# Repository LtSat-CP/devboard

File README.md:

# devboard
DevBoard releases from LtSat

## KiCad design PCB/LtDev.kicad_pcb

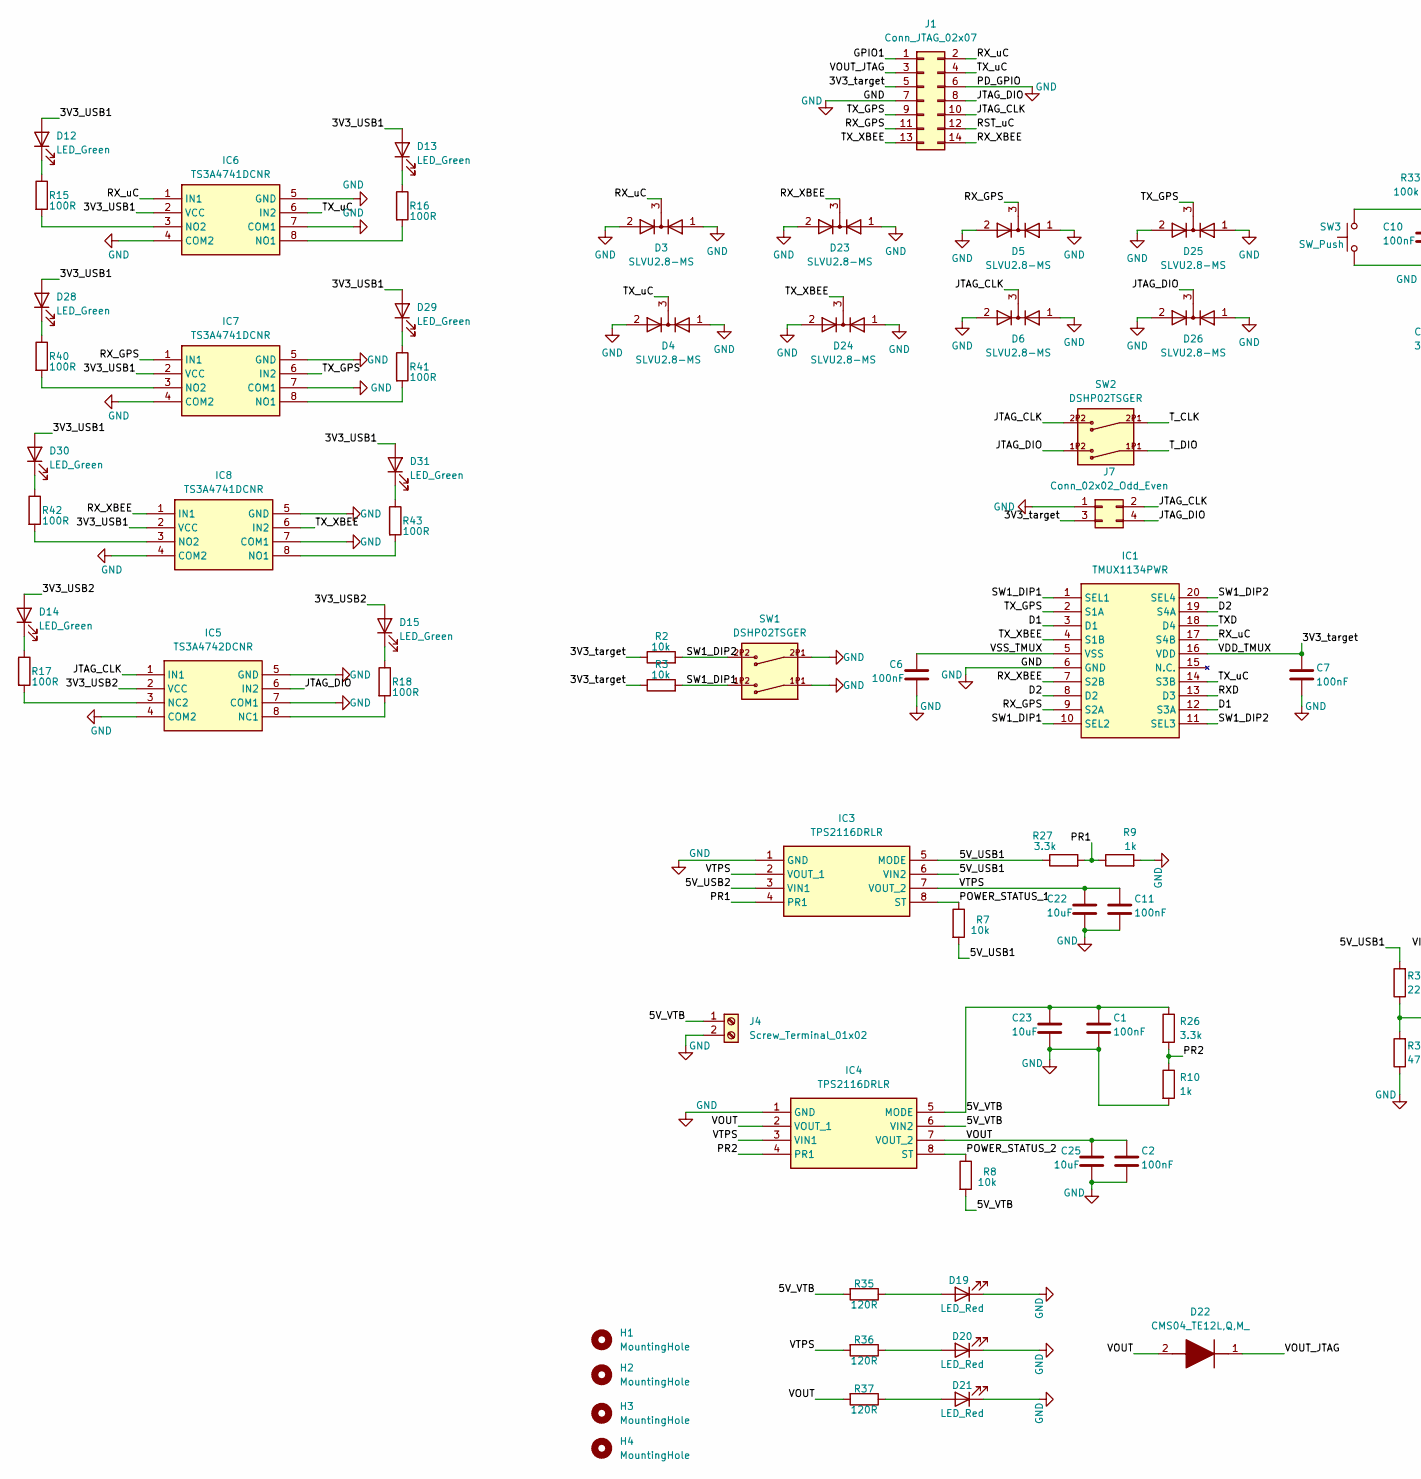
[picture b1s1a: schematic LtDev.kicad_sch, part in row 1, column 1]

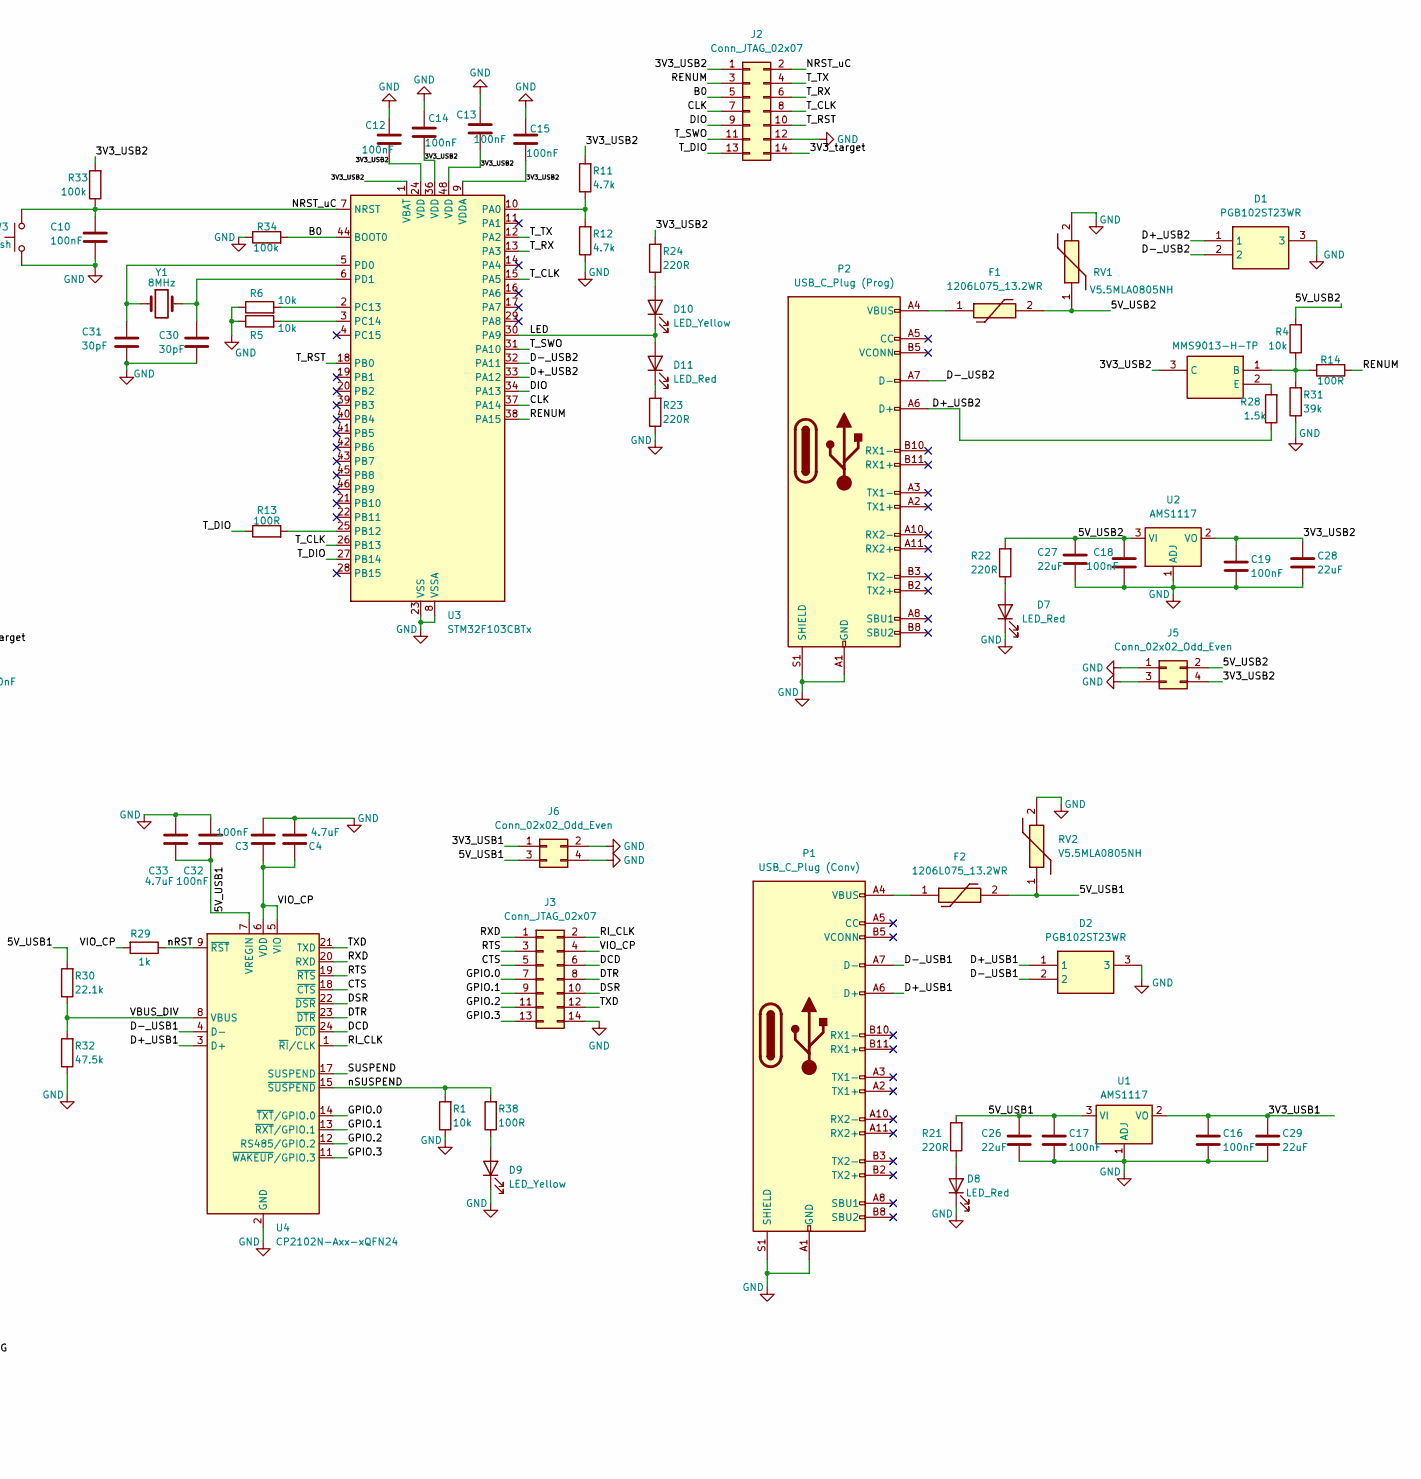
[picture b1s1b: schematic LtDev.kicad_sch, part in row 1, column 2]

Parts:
C1, C2, C3, C6, C7, C10, C11, C12, C13, C14, C15, C16, C17, C18, C19, C32: 100nF; C_0805_2012Metric
C4, C33: 4.7uF; C_0805_2012Metric
C22, C23, C25: 10uF; C_0805_2012Metric
C26, C27, C28, C29: 22uF; C_0805_2012Metric
C30, C31: 30pF; C_0805_2012Metric
D1, D2: PGB102ST23WR; SOD23_LTF; Mouser Part Number 576-PGB102ST23WR
D3, D4, D5, D6, D23, D24, D25, D26: SLVU2.8-MS; SOT-23
D7, D8, D11, D19, D20, D21: LED_Red; LED_0805_2012Metric
D9, D10: LED_Yellow; LED_0805_2012Metric
D12, D13, D14, D15, D28, D29, D30, D31: LED_Green; LED_0805_2012Metric
D22: CMS04_TE12L,Q,M_; SODFL4724X108N; Mouser Part Number 757-CMS04TE12L,Q,M
F1, F2: 1206L075_13.2WR; 1206L075132WR; Mouser Part Number 576-1206L075/13.2WR
H1, H2, H3, H4: MountingHole; MountingHole_2.2mm_M2
IC1: TMUX1134PWR; IC_TMUX1134PWR; Mouser Part Number 595-TMUX1134PWR
IC2: MMS9013-H-TP; QPNP1B2E3C_SOT-23_MCC; Mouser Part Number 833-MMS9013-H-TP
IC3, IC4: TPS2116DRLR; SOTFL50P160X60-8N; Mouser Part Number 595-TPS2116DRLR
IC5: TS3A4742DCNR; SOT65P280X145-8N; Mouser Part Number 595-TS3A4742DCNR
IC6, IC7, IC8: TS3A4741DCNR; SOT65P280X145-8N; Mouser Part Number 595-TS3A4741DCNR
J1: Conn_JTAG_02x07; PinHeader_2x07_P1.27mm_Vertical_SMD
J2, J3: Conn_JTAG_02x07; PinHeader_2x07_P2.54mm_Vertical_SMD
J4: Screw_Terminal_01x02; TerminalBlock_bornier-2_P5.08mm
J5, J6, J7: Conn_02x02_Odd_Even; PinHeader_2x02_P2.54mm_Vertical_SMD
P1: USB_C_Plug (Conv); AMPHENOL_12401610E4_2A
P2: USB_C_Plug (Prog); AMPHENOL_12401610E4_2A
R1, R2, R3, R4, R5, R6, R7, R8: 10k; R_0805_2012Metric
R9, R10, R29: 1k; R_0805_2012Metric
R11, R12: 4.7k; R_0805_2012Metric
R13, R14, R15, R16, R17, R18, R38, R40, R41, R42, R43: 100R; R_0805_2012Metric
R21, R22, R23, R24: 220R; R_0805_2012Metric
R26, R27: 3.3k; R_0805_2012Metric
R28: 1.5k; R_0805_2012Metric
R30: 22.1k; R_0805_2012Metric
R31: 39k; R_0805_2012Metric
R32: 47.5k; R_0805_2012Metric
R33, R34: 100k; R_0805_2012Metric
R35, R36, R37: 120R; R_0805_2012Metric
RV1, RV2: V5.5MLA0805NH; VARC2012X110N; Mouser Part Number 576-V5.5MLA0805NH
SW1, SW2: DSHP02TSGER
SW3: SW_Push; SW_Push_SPST_NO_Alps_SKRK
U1, U2: AMS1117; SOT-223-3_TabPin2
U3: STM32F103CBTx; LQFP-48_7x7mm_P0.5mm
U4: CP2102N-Axx-xQFN24; QFN-24-1EP_4x4mm_P0.5mm_EP2.6x2.6mm
Y1: 8MHz; XTAL_MSB2GI_YXC

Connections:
/3V3_USB1: C16.1, C29.1, D12.2 (A), D13.2 (A), D28.2 (A), D29.2 (A), D30.2 (A), D31.2 (A), IC6.2 (VCC), IC7.2 (VCC), IC8.2 (VCC), J6.1, U1.2 (VO)
/3V3_USB2: C12.2, C13.2, C14.2, C15.2, C19.1, C28.1, D14.2 (A), D15.2 (A), IC2.3 (C), IC5.2 (VCC), J2.1, J5.4, R11.2, R24.2, R33.2, U2.2 (VO), U3.1 (VBAT), U3.9 (VDDA), U3.24 (VDD), U3.36 (VDD), U3.48 (VDD)
/3V3_target: C7.1, IC1.16 (VDD), J1.5, J2.14, J7.3, R2.1, R3.1
/5V_USB1: C17.1, C26.1, C32.2, C33.2, F2.2, IC3.5 (MODE), IC3.6 (VIN2), J6.3, R7.2, R21.2, R27.1, R30.2, RV2.1, U1.3 (VI), U4.7 (VREGIN)
/5V_USB2: C18.1, C27.1, F1.2, IC3.3 (VIN1), J5.2, R4.2, R22.2, RV1.1, U2.3 (VI)
/5V_VTB: C1.1, C23.1, IC4.5 (MODE), IC4.6 (VIN2), J4.1, R8.2, R26.1, R35.2
/B0: J2.5, R34.2, U3.44 (BOOT0)
/CLK: J2.7, U3.37 (PA14)
/CTS: J3.5, U4.18 (~CTS)
/D1: IC1.3 (D1), IC1.12 (S3A)
/D2: IC1.8 (D2), IC1.19 (S4A)
/D+_USB1: D2.1, P1.A6 (D+), U4.3 (D+)
/D+_USB2: D1.1, P2.A6 (D+), R28.1, U3.33 (PA12)
/D-_USB1: D2.2, P1.A7 (D-), U4.4 (D-)
/D-_USB2: D1.2, P2.A7 (D-), U3.32 (PA11)
/DCD: J3.6, U4.24 (~DCD)
/DIO: J2.9, U3.34 (PA13)
/DSR: J3.10, U4.22 (~DSR)
/DTR: J3.8, U4.23 (~DTR)
/GPIO1: J1.1
/GPIO.0: J3.7, U4.14 (~TXT/GPIO.0)
/GPIO.1: J3.9, U4.13 (~RXT/GPIO.1)
/GPIO.2: J3.11, U4.12 (RS485/GPIO.2)
/GPIO.3: J3.13, U4.11 (~WAKEUP/GPIO.3)
/JTAG_CLK: D6.3 (K), IC5.1 (IN1), J1.10, J7.2, SW2.2P2
/JTAG_DIO: D26.3 (K), IC5.6 (IN2), J1.8, J7.4, SW2.1P2
/LED: D10.1 (K), D11.2 (A), U3.30 (PA9)
/NRST_uC: C10.1, J2.2, R33.1, SW3.2, U3.7 (NRST)
/POWER_STATUS_1: IC3.8 (ST), R7.1
/POWER_STATUS_2: IC4.8 (ST), R8.1
/PR1: IC3.4 (PR1), R9.1, R27.2
/PR2: IC4.4 (PR1), R10.1, R26.2
/RENUM: J2.3, R14.1, U3.38 (PA15)
/RI_CLK: J3.2, U4.1 (~RI/CLK)
/RST_uC: J1.12
/RTS: J3.3, U4.19 (~RTS)
/RXD: IC1.13 (D3), J3.1, U4.20 (RXD)
/RX_GPS: D5.3 (K), IC1.9 (S2A), IC7.1 (IN1), J1.11
/RX_XBEE: D23.3 (K), IC1.7 (S2B), IC8.1 (IN1), J1.14
/RX_uC: D3.3 (K), IC1.17 (S4B), IC6.1 (IN1), J1.2
/SUSPEND: U4.17 (SUSPEND)
/SW1_DIP1: IC1.1 (SEL1), IC1.10 (SEL2), R3.2, SW1.1P2
/SW1_DIP2: IC1.11 (SEL3), IC1.20 (SEL4), R2.2, SW1.2P2
/TXD: IC1.18 (D4), J3.12, U4.21 (TXD)
/TX_GPS: D25.3 (K), IC1.2 (S1A), IC7.6 (IN2), J1.9
/TX_XBEE: D24.3 (K), IC1.4 (S1B), IC8.6 (IN2), J1.13
/TX_uC: D4.3 (K), IC1.14 (S3B), IC6.6 (IN2), J1.4
/T_CLK: J2.8, SW2.2P1, U3.15 (PA5), U3.26 (PB13)
/T_DIO: J2.13, R13.1, SW2.1P1, U3.27 (PB14)
/T_RST: J2.10, U3.18 (PB0)
/T_RX: J2.6, U3.13 (PA3)
/T_SWO: J2.11, U3.31 (PA10)
/T_TX: J2.4, U3.12 (PA2)
/VBUS_DIV: R30.1, R32.2, U4.8 (VBUS)
/VIO_CP: C3.1, C4.1, J3.4, R29.2, U4.5 (VIO), U4.6 (VDD)
/VOUT: C2.1, C25.1, D22.2 (A), IC4.2 (VOUT_1), IC4.7 (VOUT_2), R37.2
/VOUT_JTAG: D22.1 (K), J1.3
/VSS_TMUX: C6.1, IC1.5 (VSS)
/VTPS: C11.1, C22.1, IC3.2 (VOUT_1), IC3.7 (VOUT_2), IC4.3 (VIN1), R36.2
/nRST: R29.1, U4.9 (~RST)
/nSUSPEND: R1.2, R38.2, U4.15 (~SUSPEND)
GND: C1.2, C2.2, C3.2, C4.2, C6.2, C7.2, C10.2, C11.2, C12.1, C13.1, C14.1, C15.1, C16.2, C17.2, C18.2, C19.2, C22.2, C23.2, C25.2, C26.2, C27.2, C28.2, C29.2, C30.2, C31.2, C32.1, C33.1, D1.3, D2.3, D3.1 (A), D3.2 (A), D4.1 (A), D4.2 (A), D5.1 (A), D5.2 (A), D6.1 (A), D6.2 (A), D7.1 (K), D8.1 (K), D9.1 (K), D19.1 (K), D20.1 (K), D21.1 (K), D23.1 (A), D23.2 (A), D24.1 (A), D24.2 (A), D25.1 (A), D25.2 (A), D26.1 (A), D26.2 (A), IC1.6 (GND), IC3.1 (GND), IC4.1 (GND), IC5.4 (COM2), IC5.5 (GND), IC5.7 (COM1), IC6.4 (COM2), IC6.5 (GND), IC6.7 (COM1), IC7.4 (COM2), IC7.5 (GND), IC7.7 (COM1), IC8.4 (COM2), IC8.5 (GND), IC8.7 (COM1), J1.6, J1.7, J2.12, J3.14, J4.2, J5.1, J5.3, J6.2, J6.4, J7.1, P1.A1 (GND), P1.A12 (GND), P1.B1 (GND), P1.B12 (GND), P1.S1 (SHIELD), P2.A1 (GND), P2.A12 (GND), P2.B1 (GND), P2.B12 (GND), P2.S1 (SHIELD), R1.1, R5.1, R6.1, R9.2, R10.2, R12.1, R23.1, R31.1, R32.1, R34.1, RV1.2, RV2.2, SW1.1P1, SW1.2P1, SW3.1, U1.1 (ADJ), U2.1 (ADJ), U3.8 (VSSA), U3.23 (VSS), U3.35 (VSS), U3.47 (VSS), U4.2 (GND), U4.25 (GND)
unnamed: D7.2 (A), R22.1
unnamed: D8.2 (A), R21.1
unnamed: D9.2 (A), R38.1
unnamed: D10.2 (A), R24.1
unnamed: D11.1 (K), R23.2
unnamed: D12.1 (K), R15.1
unnamed: D13.1 (K), R16.1
unnamed: D14.1 (K), R17.1
unnamed: D15.1 (K), R18.1
unnamed: D19.2 (A), R35.1
unnamed: D20.2 (A), R36.1
unnamed: D21.2 (A), R37.1
unnamed: D28.1 (K), R40.1
unnamed: D29.1 (K), R41.1
unnamed: D30.1 (K), R42.1
unnamed: D31.1 (K), R43.1
unnamed: F1.1, P2.A4 (VBUS), P2.A9 (VBUS), P2.B4 (VBUS), P2.B9 (VBUS)
unnamed: F2.1, P1.A4 (VBUS), P1.A9 (VBUS), P1.B4 (VBUS), P1.B9 (VBUS)
unnamed: IC2.1 (B), R4.1, R14.2, R31.2
unnamed: IC2.2 (E), R28.2
unnamed: IC5.8 (NC1), R18.2
unnamed: IC5.3 (NC2), R17.2
unnamed: IC6.8 (NO1), R16.2
unnamed: IC6.3 (NO2), R15.2
unnamed: IC7.8 (NO1), R41.2
unnamed: IC7.3 (NO2), R40.2
unnamed: IC8.8 (NO1), R43.2
unnamed: IC8.3 (NO2), R42.2
unnamed: R11.1, R12.2, U3.10 (PA0)
unnamed: R13.2, U3.25 (PB12)
unnamed: R6.2, U3.2 (PC13)
unnamed: R5.2, U3.3 (PC14)
unnamed: C31.1, U3.5 (PD0), Y1.1
unnamed: C30.1, U3.6 (PD1), Y1.2

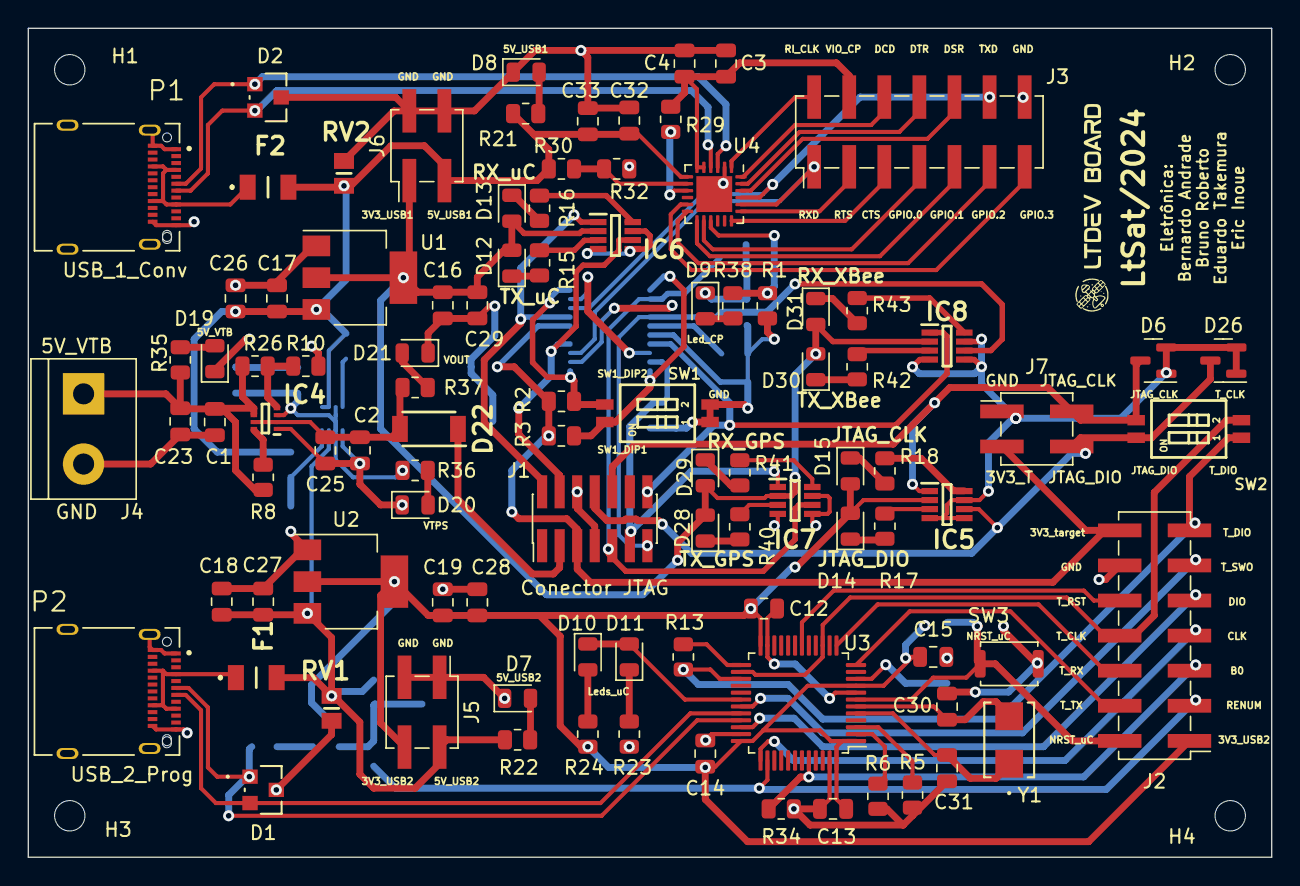
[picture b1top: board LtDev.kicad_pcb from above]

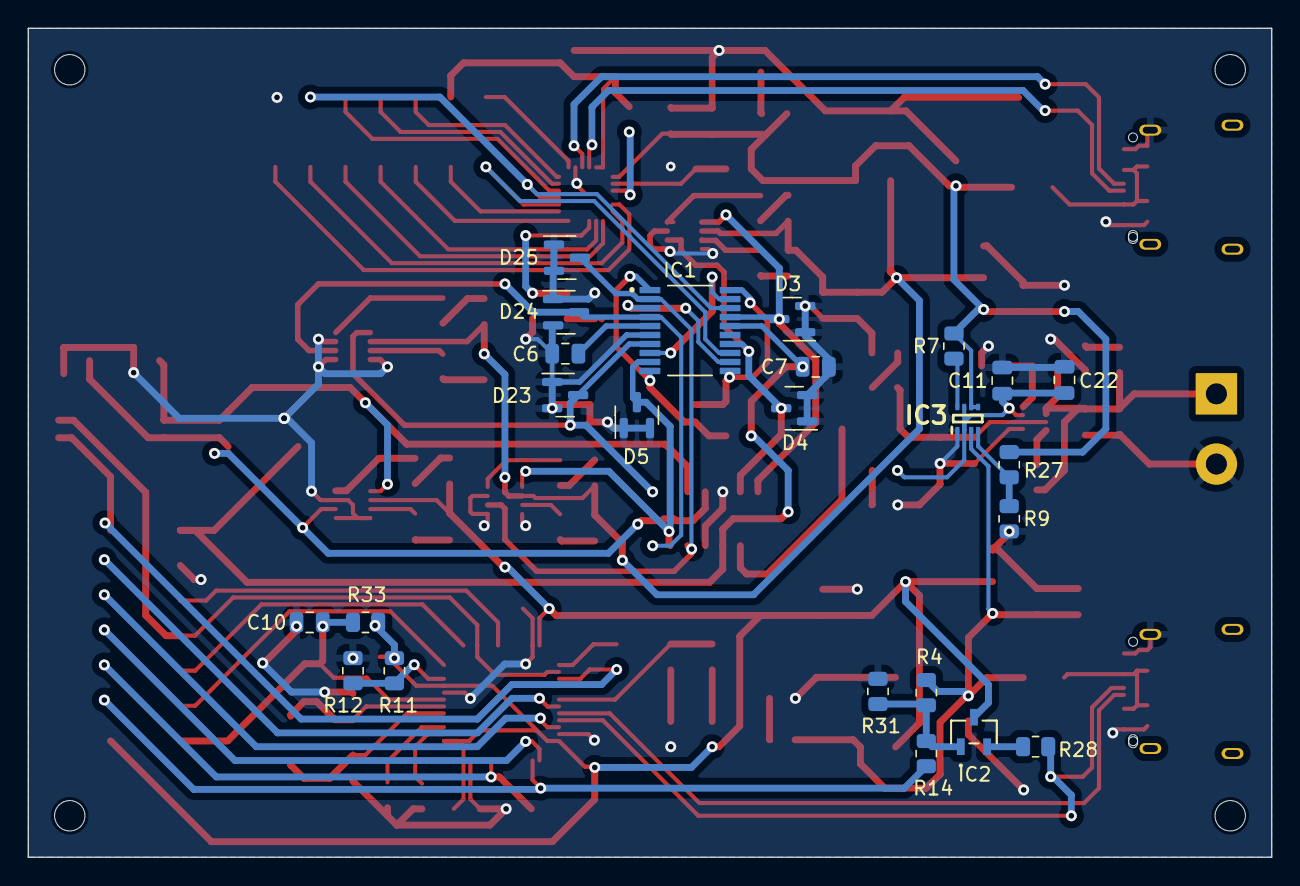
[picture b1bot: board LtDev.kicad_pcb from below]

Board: 2 copper layers, 90.0 x 60.0 mm, 126 parts (24 on the bottom side), 93 nets.

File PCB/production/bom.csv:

Designator,Footprint,Quantity,Value,LCSC Part #
"C1, C10, C11, C12, C13, C14, C15, C16, C17, C18, C19, C2, C3, C32, C6, C7",0805,16,100nF,
"C22, C23, C25",0805,3,10uF,
"C26, C27, C28, C29",0805,4,22uF,
"C30, C31",0805,2,30pF,
"C33, C4",0805,2,4.7uF,
"D1, D2",SOD23_LTF,2,PGB102ST23WR,
"D10, D9",0805,2,LED_Yellow,
"D11, D19, D20, D21, D7, D8",0805,6,LED_Red,
"D12, D13, D14, D15, D28, D29, D30, D31",0805,8,LED_Green,
D22,SODFL4724X108N,1,"CMS04_TE12L,Q,M_",
"D23, D24, D25, D26, D3, D4, D5, D6",SOT-23,8,SLVU2.8-MS,
"F1, F2",1206L075132WR,2,1206L075_13.2WR,
"H1, H2, H3, H4",MountingHole_2.2mm_M2,4,MountingHole,
IC1,IC_TMUX1134PWR,1,TMUX1134PWR,
IC2,QPNP1B2E3C_SOT-23_MCC,1,MMS9013-H-TP,
"IC3, IC4",SOTFL50P160X60-8N,2,TPS2116DRLR,
IC5,SOT65P280X145-8N,1,TS3A4742DCNR,
"IC6, IC7, IC8",SOT65P280X145-8N,3,TS3A4741DCNR,
J1,PinHeader_2x07_P1.27mm_Vertical_SMD,1,Conn_JTAG_02x07,
"J2, J3",PinHeader_2x07_P2.54mm_Vertical_SMD,2,Conn_JTAG_02x07,
J4,TerminalBlock_bornier-2_P5.08mm,1,Screw_Terminal_01x02,
"J5, J6, J7",PinSocket_2x02_P2.54mm_Vertical_SMD,3,Conn_02x02_Odd_Even,
P1,AMPHENOL_12401610E4_2A,1,USB_C_Plug (Conv),
P2,AMPHENOL_12401610E4_2A,1,USB_C_Plug (Prog),
"R1, R2, R3, R4, R5, R6, R7, R8",0805,8,10k,
"R10, R29, R9",0805,3,1k,
"R11, R12",0805,2,4.7k,
"R13, R14, R15, R16, R17, R18, R38, R40, R41, R42, R43",0805,11,100R,
"R21, R22, R23, R24",0805,4,220R,
"R26, R27",0805,2,3.3k,
R28,0805,1,1.5k,
R30,0805,1,22.1k,
R31,0805,1,39k,
R32,0805,1,47.5k,
"R33, R34",0805,2,100k,
"R35, R36, R37",0805,3,120R,
"RV1, RV2",VARC2012X110N,2,V5.5MLA0805NH,
"SW1, SW2",SW_DIP_SPSTx02_Slide_Copal_CHS-02A_W5.08mm_P1.27mm_JPin,2,SW_DIP_x02,
SW3,SW_Push_SPST_NO_Alps_SKRK,1,SW_Push,
"U1, U2",SOT-223-3_TabPin2,2,AMS1117,
U3,LQFP-48_7x7mm_P0.5mm,1,STM32F103CBTx,
U4,QFN-24-1EP_4x4mm_P0.5mm_EP2.6x2.6mm,1,CP2102N-Axx-xQFN24,
Y1,XTAL_MSB2GI_YXC,1,8MHz,

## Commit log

2024-04-17 1.0.1
2024-05-05 Add files via upload
    1.1.0
2024-05-07 v.1.1.2
